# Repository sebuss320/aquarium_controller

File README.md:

# aquarium_controller
The prototype of the controller supervising the operation of the aquarium with the use of the Arduino NANO microcontroller. Measurement of temperature, pH, liquid turbidity, illuminance, RTC module, control of the relay and stepper motor. This device was designed with Autodesk Eagle.

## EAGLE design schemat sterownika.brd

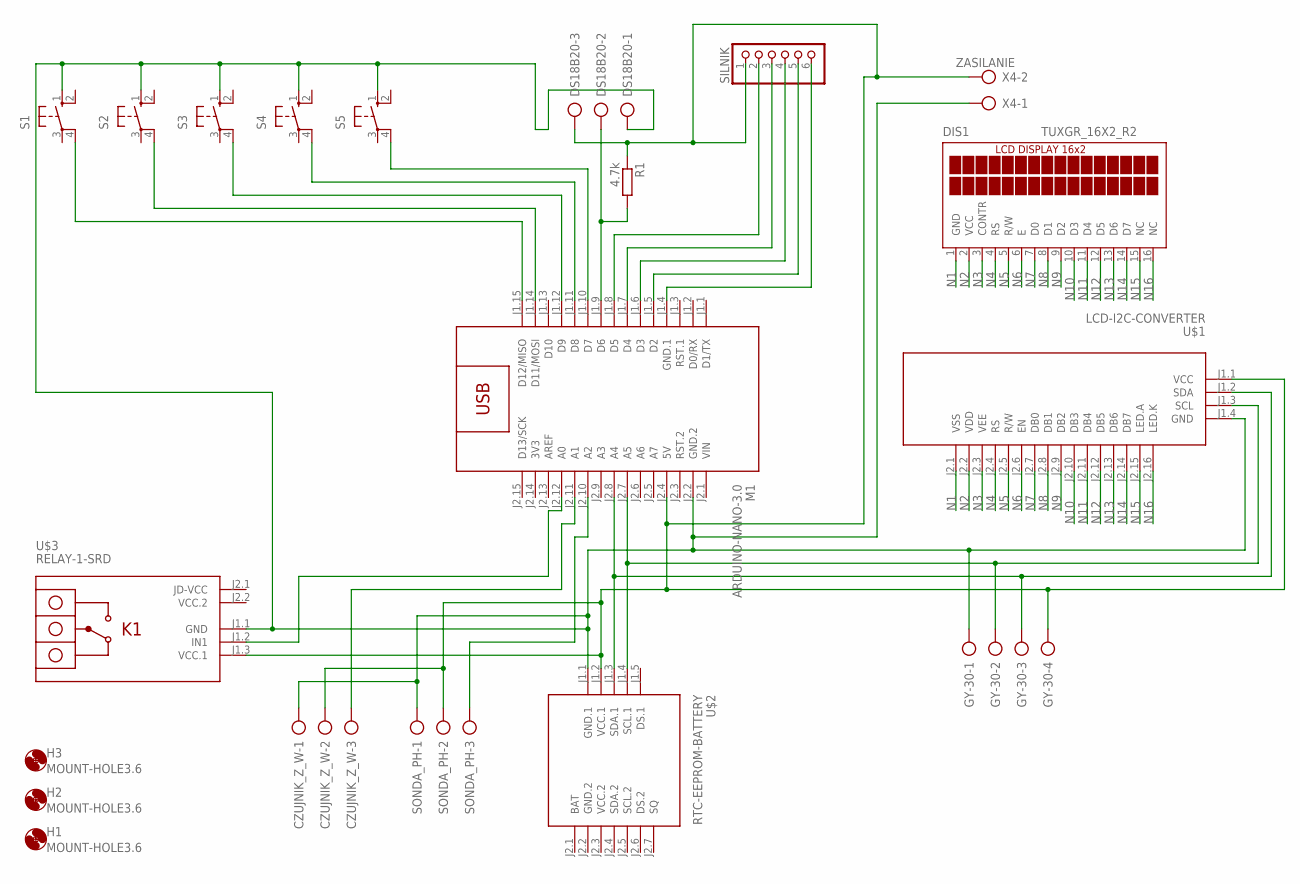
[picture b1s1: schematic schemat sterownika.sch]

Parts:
CZUJNIK_Z_W: AK500/3
DIS1: TUXGR_16X2_R2
DS18B20: AK500/3
GY-30: AK500/4
H1, H2, H3: MOUNT-HOLE3.6; 3,6
M1: ARDUINO-NANO-3.0
R1: 4.7k; 0204/7
S1, S2, S3, S4, S5: 10-XX; B3F-10XX
SILNIK: PINHD-1X6; 1X06
SONDA_PH: AK500/3
U$1: LCD-I2C-CONVERTER
U$2: RTC-EEPROM-BATTERY
U$3: RELAY-1-SRD
X4: ZASILANIE; AK500/2

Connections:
3V3: M1.J2.14 (3V3)
GND: U$1.J2.1 (VSS)
GND.2: U$2.J2.2 (GND.2)
N1: DIS1.1 (GND), U$1.J2.1 (VSS)
N2: DIS1.2 (VCC), U$1.J2.2 (VDD)
N3: DIS1.3 (CONTR), U$1.J2.3 (VEE)
N4: DIS1.4 (RS), U$1.J2.4 (RS)
N5: DIS1.5 (R/W), U$1.J2.5 (R/W)
N6: DIS1.6 (E), U$1.J2.6 (EN)
N7: DIS1.7 (D0), U$1.J2.7 (DB0)
N8: DIS1.8 (D1), U$1.J2.8 (DB1)
N9: DIS1.9 (D2), U$1.J2.9 (DB2)
N10: DIS1.10 (D3), U$1.J2.10 (DB3)
N11: DIS1.11 (D4), U$1.J2.11 (DB4)
N12: DIS1.12 (D5), U$1.J2.12 (DB5)
N13: DIS1.13 (D6), U$1.J2.13 (DB6)
N14: DIS1.14 (D7), U$1.J2.14 (DB7)
N15: DIS1.15 (NC), U$1.J2.15 (LED.A)
N16: DIS1.16 (NC), U$1.J2.16 (LED.K)
unnamed: CZUJNIK_Z_W.1, DS18B20.1, GY-30.1, M1.J2.2 (GND.2), S1.1 (S), S2.1 (S), S3.1 (S), S4.1 (S), S5.1 (S), SONDA_PH.1, U$1.J1.4 (GND), U$2.J1.1 (GND.1), U$3.J1.1 (GND), X4.1
unnamed: M1.J2.10 (A2), SONDA_PH.3
unnamed: CZUJNIK_Z_W.3, M1.J2.11 (A1)
unnamed: M1.J2.12 (A0), U$3.J1.2 (IN1)
unnamed: DS18B20.2, M1.J1.9 (D6), R1.2
unnamed: M1.J1.8 (D5), SILNIK.2
unnamed: M1.J1.7 (D4), SILNIK.3
unnamed: M1.J1.6 (D3), SILNIK.4
unnamed: M1.J1.5 (D2), SILNIK.5
unnamed: M1.J1.4 (GND.1), SILNIK.6
unnamed: CZUJNIK_Z_W.2, DS18B20.3, GY-30.4, M1.J2.4 (5V), R1.1, SILNIK.1, SONDA_PH.2, U$1.J1.1 (VCC), U$2.J1.2 (VCC.1), U$3.J1.3 (VCC.1), X4.2
unnamed: M1.J1.10 (D7), S5.4 (P1)
unnamed: M1.J1.11 (D8), S4.4 (P1)
unnamed: M1.J1.12 (D9), S3.4 (P1)
unnamed: M1.J1.14 (D11/MOSI), S2.4 (P1)
unnamed: M1.J1.15 (D12/MISO), S1.4 (P1)
unnamed: GY-30.2, M1.J2.7 (A5), U$1.J1.3 (SCL), U$2.J1.4 (SCL.1)
unnamed: GY-30.3, M1.J2.8 (A4), U$1.J1.2 (SDA), U$2.J1.3 (SDA.1)
VCC.2: U$2.J2.3 (VCC.2), U$3.J2.2 (VCC.2)
VIN: M1.J2.1 (VIN)

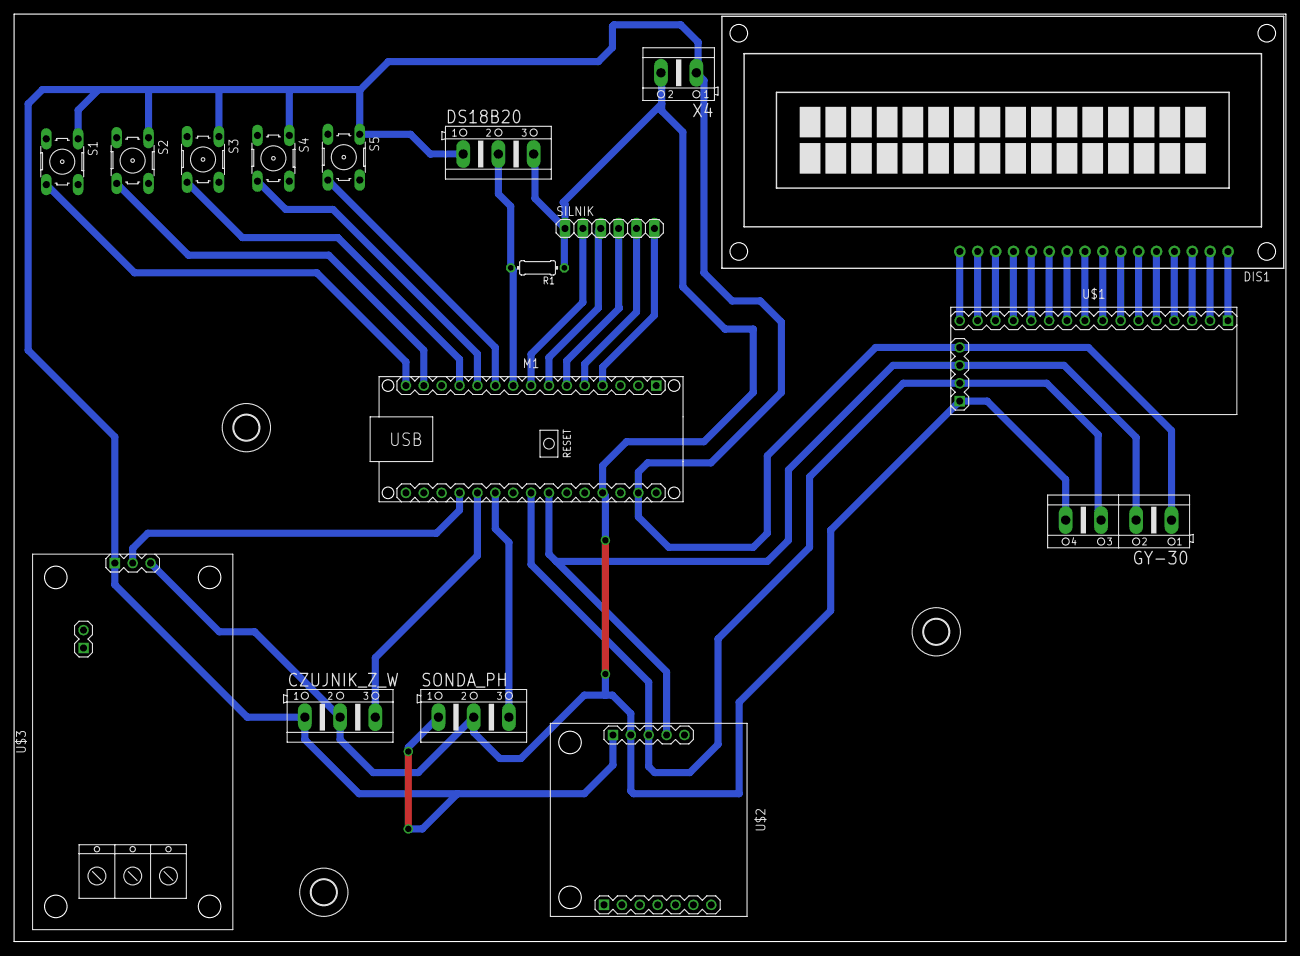
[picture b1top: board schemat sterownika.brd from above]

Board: 2 copper layers, 180.7 x 131.8 mm, 20 parts (0 on the bottom side), 35 nets.

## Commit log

2021-04-02 add finished project
2021-04-02 image

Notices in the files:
parts and their libraries:
elementy_Arduino: Released under the Creative Commons Attribution 4.0 International License: http://creativecommons.org/licenses/by/4.0
